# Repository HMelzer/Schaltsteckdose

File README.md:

# Funkschaltsteckdose für HomeMatic/RaspberryMatik

## Gehäuse
Auf der Basis des [ELV-Gehäuses OM54](https://de.elv.com/elv-design-stecker-steckdosen-gehaeuse-om-54-c-mit-tasterstoessel-und-led-leuchtfeld-083421)
und des dazugehörigen [Steckdoseneinsatzes](https://de.elv.com/schutzkontakt-stecker-steckdosen-einsatz-ohne-sicherungshalter-083422) wird hier eine Funk-Schaltsteckdose vorgestellt,
die auf der Grundlage von AsksinPP arbeitet und voll in das HomeMatic/RaspberryMatik-Programm integriert werden kann.

## Platine
Die Platine wurde mit KICAD entwickelt, die KICAD-Daten sind hier beigefügt.
Das nachfolgende Bild zeigt Vorder- und Rückseite der Leiterplatte, hier noch im Leiterplattenrahmen,
aus dem man die Leiterplatten spätestens dann trennen muss, wenn man den Steckdoseneinsatz montieren will.

## Schaltung
Für die Stromversorgung wurde ein Baustein von Hi-Link verwendet, der primärseitig mit 100 - 240 V gespeist werden und sekundärseitig 12 V DC bei 0,25 A liefern kann.
[HMK-PM12](https://de.aliexpress.com/item/32960181700.html?spm=a2g0s.9042311.0.0.19304c4d0xYQv4).
Wegen der engen Platzverhältnisse kam ein Relais G6B-2214P der Fa. Omron mit 12 V Spulenspannung zum Einsatz, dass 5 A schalten kann.<br/>
Herzstück ist, wie in den meisten HomeMatic/RaspberryMatic-Projekten, ein ArduinoProMini in der 3,3 V - Variante, der eine große Verbreitung erlangt hat und bei vielen Anbietern zu bekommen ist.
Die erforderliche Spannung für diesen und den Sendebaustein erzeugt ein LDO aus der 12 V - Spannung.<br/>
Im Schaltplan sind alternativ zwei Sendebausteine aufgeführt.
Das ist zum einen der klassische CC1101, der in vielen Projekten zur Anwendung kommt.
Da es damit in der Vergangenheit immer wieder zu Problemen mit der Sende-/Empfangsfrequenz gekommen ist, vergleiche [Fehlerhafte CC1101 Module](https://asksinpp.de/Grundlagen/FAQ/Fehlerhafte_CC1101.html),
wurde hier in der praktische Ausführung ein anderes Modul, welches ebenfalls den CC1101 verwendet, eingesetzt.
Das Modul ist ein [E07_868MS10](http://www.ebyte.com/en/product-view-news.aspx?id=180) der Fa. Ebyte.

## Ausführung/Montage
Beim Zusammenfügen des Gehäuses und des Steckdoseneinsatzes hat es sich gezeigt, dass die Öffnung im Gehäusedeckel geringfügig nachgearbeitet werden muss, um den Steckdoseneinsatz passfähig montieren zu können.
Mit dem Gehäuse lose mitgeliefert werden der Tastereinsatz, ein Lichtleiter und ein "Knackfrosch", der als Taster dient. Beim Einsetzen des Lichtleiters in den Tastereinsatz ist ein wenig Fingerspitzengefühl erforderlich
und man sollte vorsichtig zu Werke gehen, um nichts abzubrechen.
Das Bild zeigt die Oberschale mit montiertem Taster und Lichtleiter.<p/> <p/>
Im nachfolgenden Bild sieht man die Unterschale mit der bereits montierten Leiterplatte.<p/> <p/>
Der "Knackfrosch" wurde einfach in die dafür vorgesehenen Löcher auf der Vorderseite der Leiterplatte eingesetzt und die Laschen auf der Rückseite leicht umgebogen.
**Er darf nicht verlötet werden**.
Vor den eigentlichen Lötarbeiten empfiehlt es sich, die Leiterplatte aus dem Rahmen zu lösen und den Leiterplattenrand an den ehemaligen Verbindungsstellen zu glätten. Die Passfähigkeit im Gehäuse sollte anschließend geprüft werden.
Das sollte auch im Zusammenwirken mit dem Steckdoseneinsatz erfolgen und hierbei sollten auch gleich die Kontaktstreifen des Steckdoseneinsatzes an den Stellen gekennzeichnet werden, an denen diese gekürzt werden müssen.
Alle verwendeten Bauelemente sind als THT ausgeführt, sodass sich die Lötarbeiten einfach gestalten sollten. Die Verteilung auf Vorder- und Rückseite ist dem engen Platzverhältnis geschuldet, welches durch den integrierten Taster
bedingt ist.
Eine Besonderheit stellt die LED dar, da es sich um eine Bauform handelt, die zwei LED, rot und grün, in einem Gehäuse vereinigt.
Es handelt sich hierbei um eine 3 mm Diode, die von der Leiterplattenrückseite montiert werden muss, wobei diese nicht mehr als 1 mm auf der Vorderseite hervorstehen darf, da sich ansonsten der Taster nicht tief genug drücken lässt.
Alternativ kann man allerdings auch den Lichtleiter, beispielsweise mittels Dremel, um ca. 2 mm kürzen. Die Anschlussdrähte der Diode sind dabei nahe am Gehäuse zu biegen. Auf die richtige Verschaltung der beiden Dioden ist zu achten. Im Projekt zum Einsatz kam eine **EVL 209SURSYGW** (Reichelt Elektronik).
Dafür gilt auch der Aufdruck auf der Platine.<br/>
Bevor der ArduinoProMini mit allen dafür vorgesehenen Stiften mit der Leiterplatte verlötet wird, muss man die Stiftleiste (8 x 1,27 mm) für den E07_868MS10 aufsetzen und verlöten, da die Lötpunkte unter dem Arduino zu liegen kommen.
Die Anschlussstifte für den ArduinoProMini sollten in dem Bereich, wo diese vom E07_868MS10 überdeckt werden, nicht so lang ausfallen, damit es keine Kurzschlüsse gibt. Der E07_868MS10 selbst wird dann mittels der Stiftleiste 8 x 1,27 mm
und einem einzelnen Stift für den Masseanschluss auf der Leiterplatte verlötet. Dadurch erhält der E07_868MS10 auch gleich den nötigen Abstand zur Leiterplatte.
Die erforderliche Antenne wird durch einen Schaltdraht der Länge 83 mm gebildet, welcher von oben durch das vorhandene Loch rechts neben dem "Knackfrosch" gesteckt und an dem verbliebenen Anschluss am E07_868MS10 angelötet wird.
Das freie Ende des Schaltdrahtes wird dann wechselseitig durch die vorhandenen Löcher neben und oberhalb des ArduinoProMini geführt.<p/>
Das folgende Bild zeigt die bestückte Rückseite mit bereits montiertem Steckdoseneinsatz. Die montierte LED ist gut zu erkennen, ebenso das Funkmodul und die verlegte Antenne.
Das geänderte Leiterplattenlayout oben links ist in den Daten bereits korrigiert.<p/>
<p/>
Zum Schluss wird der Steckdoseneinsatz mit der Leiterplatte verlötet. Um die spätere Passfähigkeit zu erhalten, ist es empfehlenswert, Leiterplatte und Steckdoseneinsatz in das Gehäuse einzusetzen und die Laschen oberseitig mit wenig
Lötzinn zu fixieren. Nach der Entnahme aus dem Gehäuse müssen die Laschen großflächig, sowohl auf der Ober- wie auch auf der Unterseite mit der Leiterplatte verlötet werden.

## Programmierung
Die Datei [HM-LC-Sw1-Pl-DN-R1.ino](https://github.com/HMelzer/Schaltsteckdose/blob/master/HM-LC-Sw1-Pl-DN-R1/HM-LC-Sw1-Pl-DN-R1.ino) enthält das entsprechende Programm, welches in den ArduinoProMini eingespielt werden muss.
Im Bereich ab Zeile 43 sind wie immer die entsprechenden Anpassungen für "Device ID" und "Device Serial" vorzunehmen.<br/>
Die eigentliche Programmierung erfolgt dann mittels der Programmiersoftware für den Arduino in der entsprechend neusten Version und einem FTDI Adapter FT232RL USB zu TTL.
Bei Verwendung eines solchen, beispielsweise der Fa. AZ-Delivery, kann man die daran vorhandene Stiftleiste gleich in die dafür vorgesehenen Löcher am ArduinoProMini stecken und so die Programmierung auf einfache Weise vornehmen.

## Anlernen
Nachdem man die Programmierung abgeschlossen und das Gehäuse mittels der mitgelieferten Schrauben geschlossen hat, kann man die erste Funktionsprobe vornehmen. Hat man die Schaltsteckdose mittels der Steckerstifte mit dem Stromnetz verbunden,
sollte zunächst das Ein- und wieder Ausschalten über den Taster möglich sein. Im Aus-Zustand sollte keine LED leuchten, im Ein-Zustand die grüne LED.<br/>
Das Anlernen erfolgt nun in der bekannten Weise, dass man in der Zentrale die Anlernfunktion für Geräte startet und an der Schaltsteckdose den Taster kurz betätigt (rote LED blinkt), wobei dadurch die Schaltsteckdose ebenfalls in den Anlernmodus
versetzt wird und nach kurzer Zeit die blinkende LED das Blinken einstellen sollte. Nachdem der Anlernmodus in der Zentrale abgelaufen ist, sollte sich das neue Gerät im Posteingang der Zentrale wiederfinden,
woraus es dann übernommen, eingestellt und programmiert werden kann.

## Lizenz
Der Inhalt dieses Repository unterliegt der aktuellen Lizenz nach Creative Commons - [https://creativecommons.org/licenses/by-nc-sa/4.0/deed.de](https://creativecommons.org/licenses/by-nc-sa/4.0/deed.de).

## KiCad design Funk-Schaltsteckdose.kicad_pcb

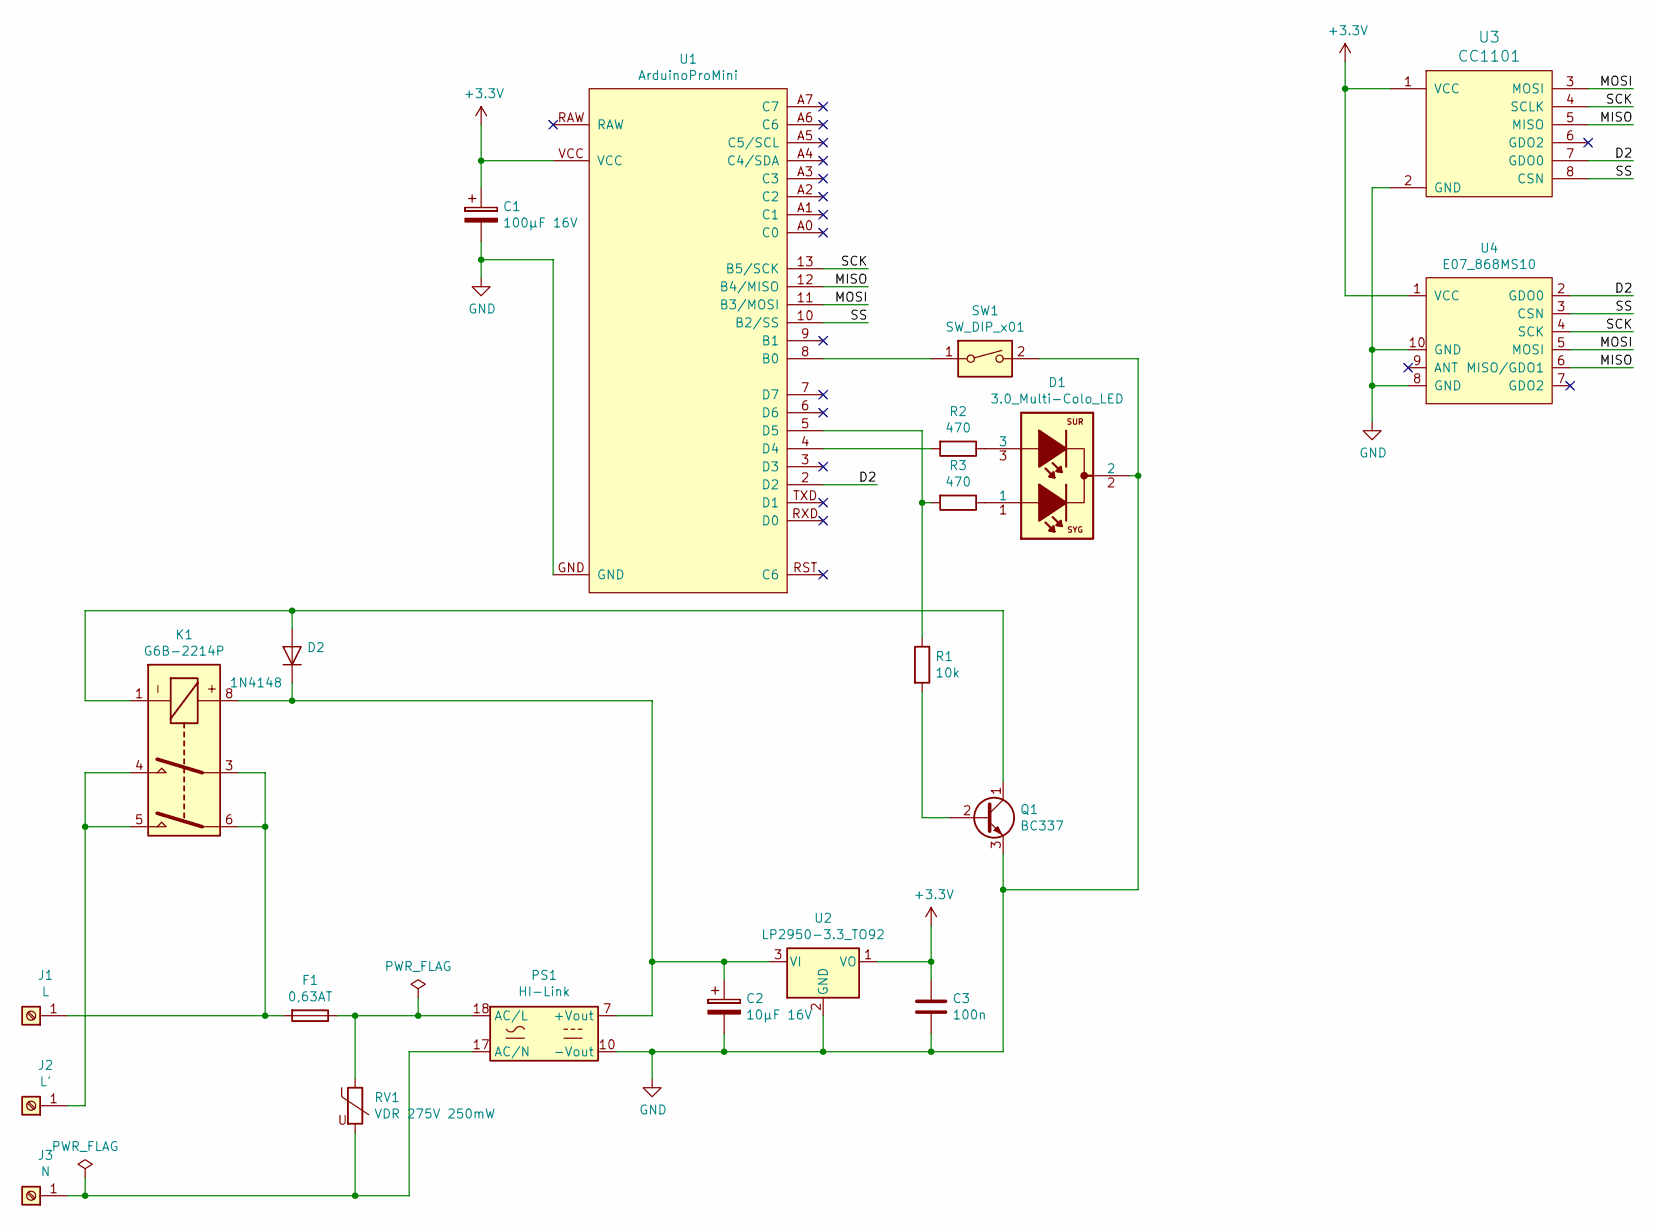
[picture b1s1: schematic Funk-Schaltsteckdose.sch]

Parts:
C1: 100µF 16V; CP_Radial_D8.0mm_P2.50mm
C2: 10µF 16V; CP_Radial_D5.0mm_P2.50mm
C3: 100n; C_Rect_L7.0mm_W6.0mm_P5.00mm
D1: 3.0_Multi-Colo_LED; Durchsteck_LED_THT_3,0
D2: 1N4148; D_DO-35_SOD27_P7.62mm_Horizontal
F1: 0,63AT; Fuseholder_TR5_Littelfuse_No560_No460
J1: L; Kontaktstreifen
J2: L'; Kontaktstreifen
J3: N; Kontaktstreifen
K1: G6B-2214P; Relay_DPST_Omron_G6B-2214
PS1: HI-Link
Q1: BC337; TO-92_Inline
R1: 10k; R_Axial_DIN0207_L6.3mm_D2.5mm_P10.16mm_Horizontal
R2, R3: 470; R_Axial_DIN0207_L6.3mm_D2.5mm_P10.16mm_Horizontal
RV1: VDR 275V 250mW; RV_Disc_D9mm_W5.2mm_P5mm
SW1: SW_DIP_x01; Schaltkontakt
U1: ArduinoProMini; ArduinoProMini_modif.
U2: LP2950-3.3_TO92; TO-92_Inline_Horizontal1
U3: CC1101
U4: E07_868MS10

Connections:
+3V3: C1.1, C3.1, U1.VCC, U2.1 (VO), U3.1 (VCC), U4.1 (VCC)
/D2: U1.2 (D2), U3.7 (GDO0), U4.2 (GDO0)
/MISO: U1.12 (B4/MISO), U3.5 (MISO), U4.6 (MISO/GDO1)
/MOSI: U1.11 (B3/MOSI), U3.3 (MOSI), U4.5 (MOSI)
/SCK: U1.13 (B5/SCK), U3.4 (SCLK), U4.4 (SCK)
/SS: U1.10 (B2/SS), U3.8 (CSN), U4.3 (CSN)
GND: C1.2, C2.2, C3.2, D1.2, PS1.10 (-Vout), Q1.3 (E), SW1.2, U1.GND, U2.2 (GND), U3.2 (GND), U4.8 (GND), U4.10 (GND)
unnamed: C2.1, D2.1 (K), K1.8, PS1.7 (+Vout), U2.3 (VI)
unnamed: D1.1, R3.1
unnamed: D1.3, R2.1
unnamed: D2.2 (A), K1.1, Q1.1 (C)
unnamed: F1.1, PS1.18 (AC/L), RV1.1
unnamed: F1.2, J1.1, K1.3, K1.6
unnamed: J2.1, K1.4, K1.5
unnamed: J3.1, PS1.17 (AC/N), RV1.2
unnamed: Q1.2 (B), R1.2
unnamed: R1.1, R3.2, U1.5 (D5)
unnamed: R2.2, U1.4 (D4)
unnamed: SW1.1, U1.8 (B0)

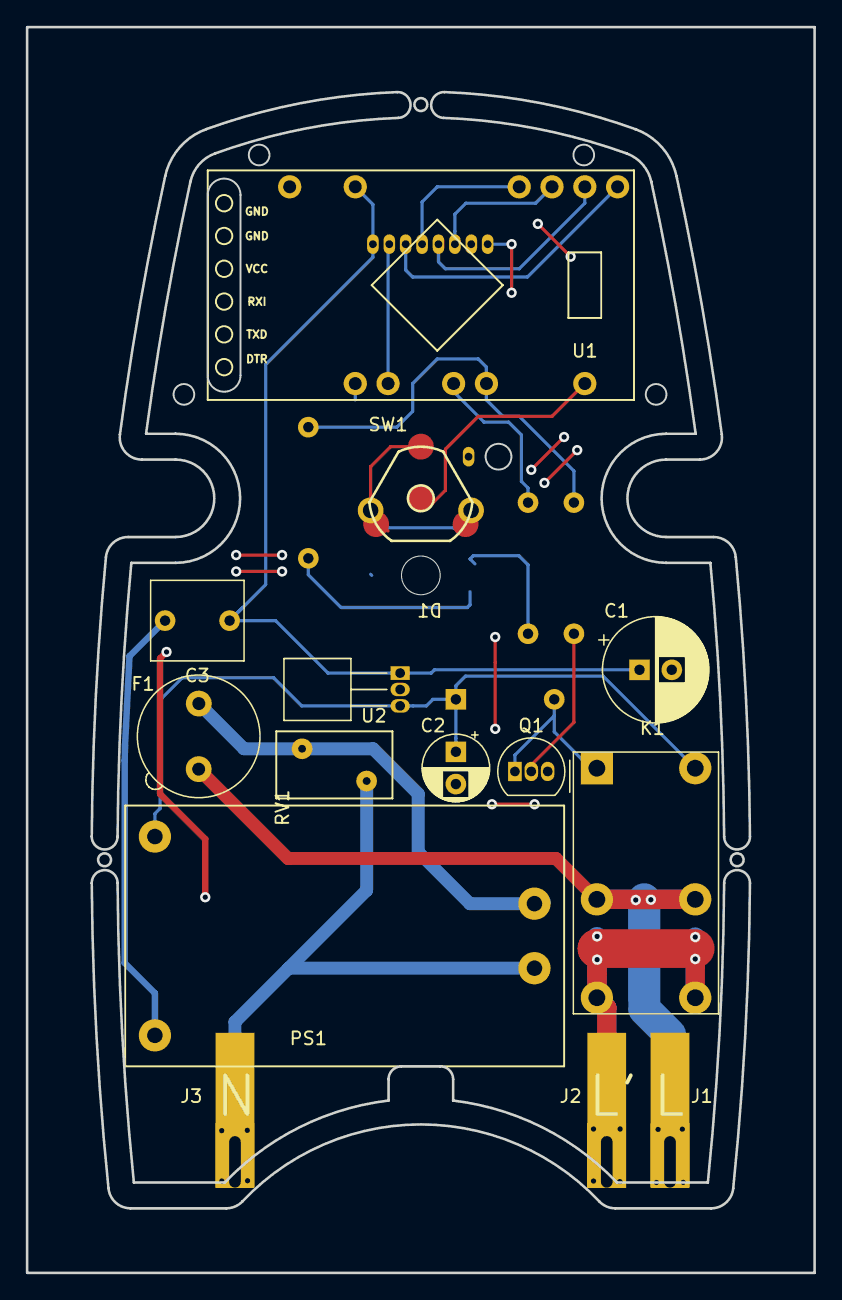
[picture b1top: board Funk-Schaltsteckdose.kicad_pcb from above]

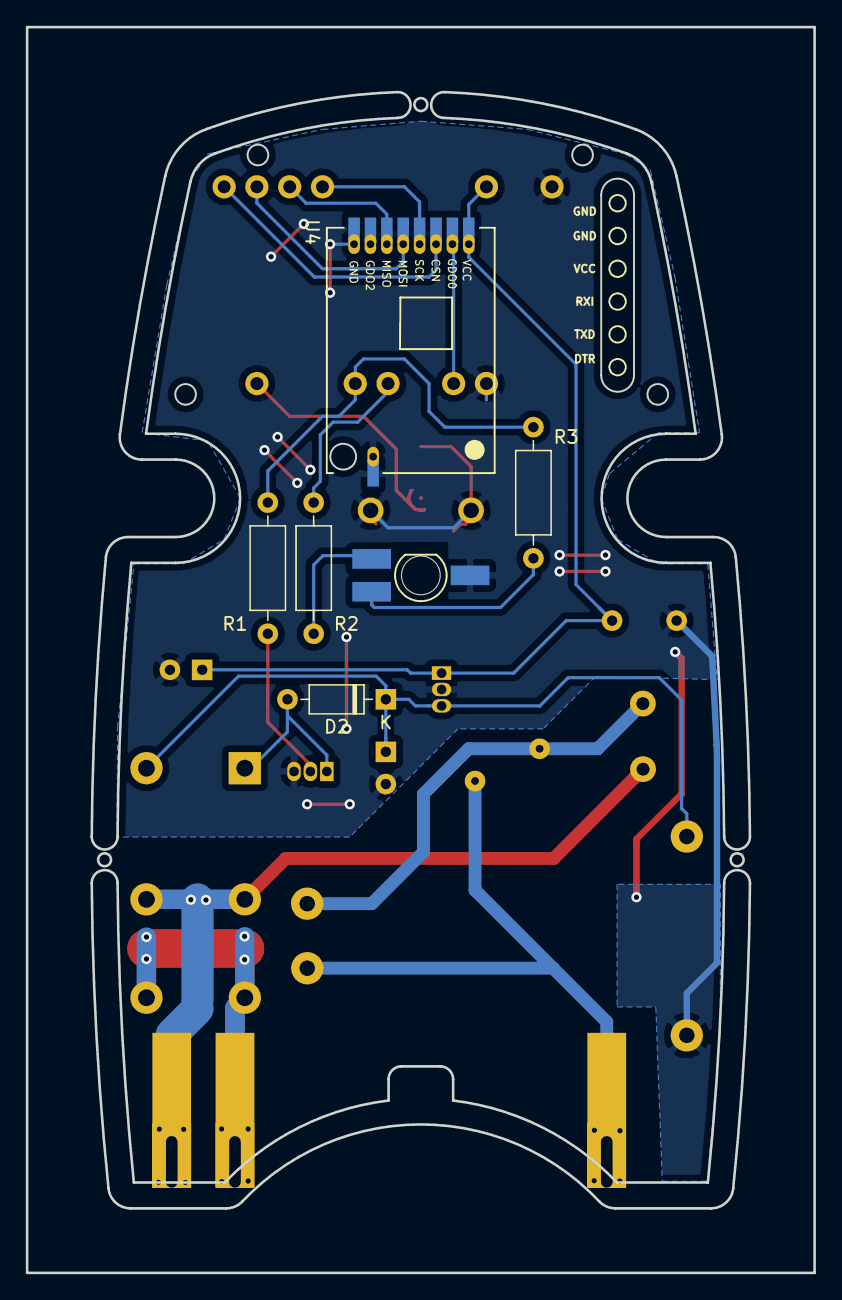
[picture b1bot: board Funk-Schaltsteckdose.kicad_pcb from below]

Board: 2 copper layers, 61.0 x 96.5 mm, 20 parts (5 on the bottom side), 19 nets.

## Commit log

2019-04-22 Alles hinzugefügt
2019-04-22 Datein gelöscht
2020-03-08 Bilder hinzugefügt
2020-03-08 Update README.md
    Geändert
2020-03-09 Layout angepasst
2020-03-09 Revert "Layout angepasst"
    This reverts commit ff7744db74a23c470d7ae99f610fa08b87265f2a.
2020-03-09 Daten angepasst
2020-03-09 Bild geändert
2020-03-22 Readme-Inhalt präzisiert
